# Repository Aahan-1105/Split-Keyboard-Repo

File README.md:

# Venturi - 48 Key Split Keyboard
*Code name: Model 901*

My first PCBs, first personal electronics project, and much more. This has been a lot of firsts so please excuse mistakes. Key inspiration is also mentioned below.

Steal from the best, invent the rest

## 

## Overview
The Venturi (aka model 901, venturi48) is a 48-key split, ergonomic keyboard. I can use lots of descriptors, but you can find that in the features section. 

## Contents
- All the KiCad files, including schematics and PCB
- All CAD Files including an assembly including all the components on the left side and cases for both
- ZMK firmware for Venturi
- Production files as used for production

## Images

### CAD Render

### Schematic (Left)

### PCB (Panelized)

## To-Do
- Triple-check that PCBs are good and needed components are accounted for
- PURCHASE
- Assemble and test!

## Features
- **48 Keys**  - All laptop keys within 2 layers, with additional layers for extra functionality. 
- **Wireless** - One less cable to worry about! 2x 110 maH LiPO Batteries, 2+ week battery life (estimated). Seamless multi-device operation.
- **Column Stagger** - Some mild colstag makes it more comfy to type on by better suting the different finger lengths
- **Keyboard Continuity** - Closer layout to a Macbook or general keyboard than most ergo KBs, so that you're not mad at all other keyboards while using this
- **Low Profile**  - Thinner = Better? More portable and less of an upward angle on the wrists, no need for a wrist rest 
- **Portable** - Easy on the go typing via a 3d print to easily carry it without risking damage in a backpack
- **Hot-Swappable** - Changed your mind on those clicky switches? Or maybe you're looking for a change of pace? The Venturi has you covered with hotswap switches!
- **Magsafe** - Not to wirelessly charge or to attach to the back of your phone, but for convenient tenting or to check if that coin is magnetic or not (it wasn't)

## BOM (For Hackclub Stardance Purposes)
|Purchase Status|Part                           |Qty|Price/per (CAD)|Total |Link                             |Shipping/Tax|Notes                    |
|---------------|-------------------------------|---|---------------|------|---------------------------------|------------|-------------------------|
|               |NRF52840 Dev Board             |2  |$3.95          |$7.90 |https://a.aliexpress.com/_mrUhUVZ|            |MC                       |
|               |MSK12C02 (20 pack)             |1  |$3.85          |$3.85 |https://a.aliexpress.com/_mLPJnJ1|            |Power Switch             |
|               |JST PH 2.0 Bent Plug (100 pack)|1  |$2.61          |$2.61 |https://a.aliexpress.com/_m0dvH4j|            |Battery Connector        |
|               |1N4148W Diode (100 pack)       |1  |$2.07          |$2.07 |https://a.aliexpress.com/_mNCQ5SX|            |Diodes                   |
|               |Choc Hotswap Socket (70 pack)  |1  |$10.48         |$10.48|https://a.aliexpress.com/_mq1DDpN|            |Hotswap Socket           |
|               |2.54mm socket (10 pack)        |1  |$2.64          |$2.64 |https://a.aliexpress.com/_mtOu6HZ|            |Sockets for MC           |
|               |KailH Choc Pro Red             |1  |$32.26         |$32.26|https://a.aliexpress.com/_mKtAtkx|            |Switch                   |
|               |301230 Battery JST             |2  |$5.19          |$10.38|https://a.aliexpress.com/_mt5WUH1|6.18        |Battery                  |
|               |JLCPCB PCB                     |1  |$17.73         |$17.73|                                 |12.37       |PCB (no link available)  |
|               |FNIRSI HS-02A Basic            |1  |$39.44         |$39.44|https://a.aliexpress.com/_mKQRvMj|            |Soldering Iron           |
|               |Magsafe Ring (6)               |1  |$7.51          |$7.51 |https://a.aliexpress.com/_mtm6duj|            |Magsafe Ring for Mounting|
|               |20g Lead-free solder           |1  |$5.29          |$5.29 |https://a.aliexpress.com/_mKjygpD|            |Soldering                |
|               |Flux Pen 10mL                  |1  |$4.98          |$4.98 |https://a.aliexpress.com/_mKjygpD|            |Flux for soldering       |
|               |                               |   |               |$0.00 |                                 |            |                         |
|               |                               |   |               |$0.00 |                                 |            |                         |
|               |TOTAL (CAD)                    |   |$165.69        |$0.00 |                                 |            |                         |
|               |TOTAL (USD)                    |   |$119.30        |$0.00 |                                 |            |                         |

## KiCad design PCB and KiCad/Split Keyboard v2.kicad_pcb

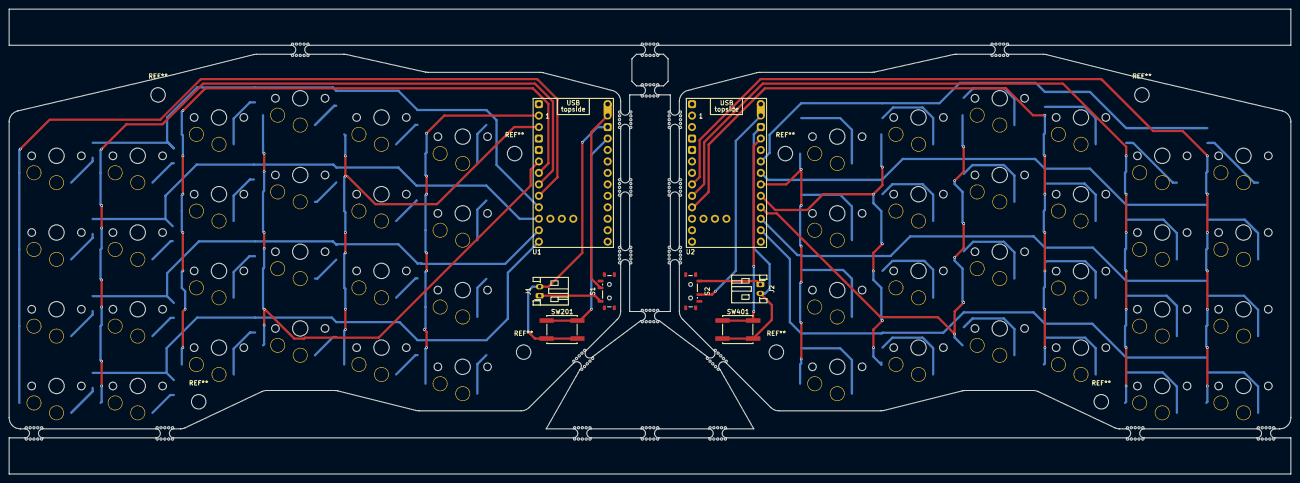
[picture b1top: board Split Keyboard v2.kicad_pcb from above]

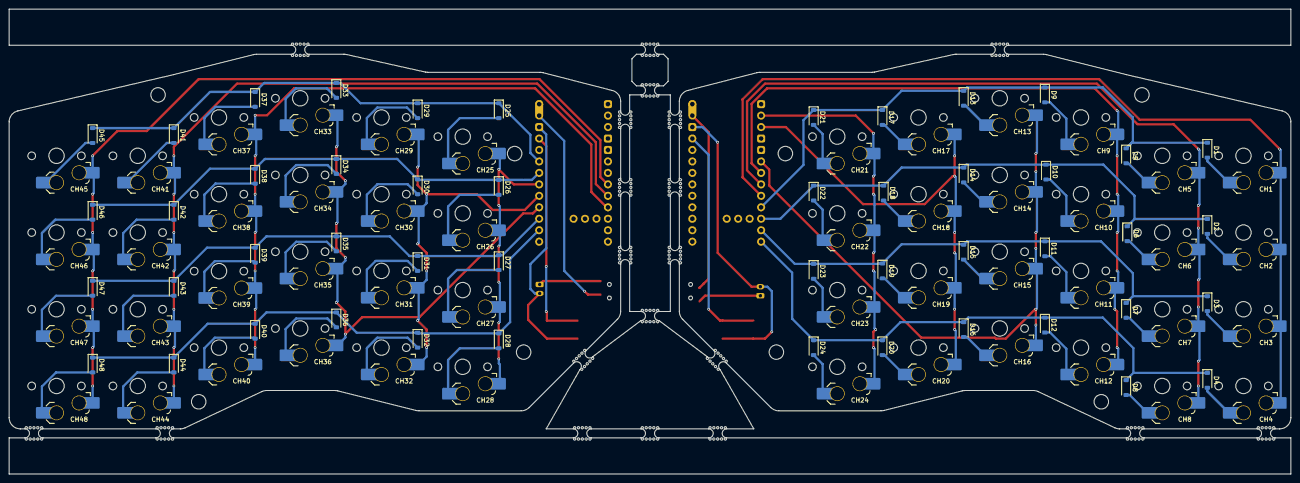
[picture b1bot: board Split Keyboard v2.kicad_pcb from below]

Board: 2 copper layers, 284.0 x 103.0 mm, 104 parts (96 on the bottom side), 76 nets.

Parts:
CH1, CH2, CH3, CH4, CH5, CH6, CH7, CH8, CH9, CH10, CH11, CH12, CH13, CH14, CH15, CH16, CH17, CH18, CH19, CH20, CH21, CH22, CH23, CH24, CH25, CH26, CH27, CH28, CH29, CH30, CH31, CH32, CH33, CH34, CH35, CH36, CH37, CH38, CH39, CH40, CH41, CH42, CH43, CH44, CH45, CH46, CH47, CH48: choc_v1_SW_HS; SW_choc_v1_HS_CPG135001S30_1u
D1, D2, D3, D4, D5, D6, D7, D8, D9, D10, D11, D12, D13, D14, D15, D16, D17, D18, D19, D20, D21, D22, D23, D24, D25, D26, D27, D28, D29, D30, D31, D32, D33, D34, D35, D36, D37, D38, D39, D40, D41, D42, D43, D44, D45, D46, D47, D48: 1N4148W; D_SOD-123
J1, J2: Conn_01x02_Socket; JST_PH_S2B-PH-K_1x02_P2.00mm_Horizontal
S1, S2: MSK12C02; SW_SPDT_Shouhan_MSK12C02
SW201, SW401: SW_SPST; SW_SPST_EVQQ2
U1, U2: nice_nano; nice_nano_AH_USBup

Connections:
/Left_Half/col1: CH21.1, CH22.1, CH23.1, CH24.1, U1.1 (P0.06)
/Left_Half/col2: CH17.1, CH18.1, CH19.1, CH20.1, U1.2 (P0.08)
/Left_Half/col3: CH13.1, CH14.1, CH15.1, CH16.1, U1.5 (P0.17)
/Left_Half/col4: CH9.1, CH10.1, CH11.1, CH12.1, U1.6 (P0.20)
/Left_Half/col5: CH5.1, CH6.1, CH7.1, CH8.1, U1.7 (P0.22)
/Left_Half/col6: CH1.1, CH2.1, CH3.1, CH4.1, U1.8 (P0.24)
/Left_Half/row1: D1.1 (K), D5.1 (K), D9.1 (K), D13.1 (K), D17.1 (K), D21.1 (K), U1.9 (P1.00)
/Left_Half/row2: D2.1 (K), D6.1 (K), D10.1 (K), D14.1 (K), D18.1 (K), D22.1 (K), U1.10 (P0.11)
/Left_Half/row3: D3.1 (K), D7.1 (K), D11.1 (K), D15.1 (K), D19.1 (K), D23.1 (K), U1.11 (P1.04-LF)
/Left_Half/row4: D4.1 (K), D8.1 (K), D12.1 (K), D16.1 (K), D20.1 (K), D24.1 (K), U1.12 (P1.06-LF)
/Right_Half/col1: CH25.1, CH26.1, CH27.1, CH28.1, U2.19 (P0.02-LF)
/Right_Half/col2: CH29.1, CH30.1, CH31.1, CH32.1, U2.20 (P1.15-LF)
/Right_Half/col3: CH33.1, CH34.1, CH35.1, CH36.1, U2.21 (P1.13-LF)
/Right_Half/col4: CH37.1, CH38.1, CH39.1, CH40.1, U2.9 (P1.00)
/Right_Half/col5: CH41.1, CH42.1, CH43.1, CH44.1, U2.8 (P0.24)
/Right_Half/col6: CH45.1, CH46.1, CH47.1, CH48.1, U2.7 (P0.22)
/Right_Half/row1: D25.1 (K), D29.1 (K), D33.1 (K), D37.1 (K), D41.1 (K), D45.1 (K), U2.17 (P0.31-LF)
/Right_Half/row2: D26.1 (K), D30.1 (K), D34.1 (K), D38.1 (K), D42.1 (K), D46.1 (K), U2.18 (P0.29-LF)
/Right_Half/row3: D27.1 (K), D31.1 (K), D35.1 (K), D39.1 (K), D43.1 (K), D47.1 (K), U2.22 (P1.11-LF)
/Right_Half/row4: D28.1 (K), D32.1 (K), D36.1 (K), D40.1 (K), D44.1 (K), D48.1 (K), U2.23 (P0.10-LF)
unnamed: CH1.2, D1.2 (A)
unnamed: CH2.2, D2.2 (A)
unnamed: CH3.2, D3.2 (A)
unnamed: CH4.2, D4.2 (A)
unnamed: CH5.2, D5.2 (A)
unnamed: CH6.2, D6.2 (A)
unnamed: CH7.2, D7.2 (A)
unnamed: CH8.2, D8.2 (A)
unnamed: CH9.2, D9.2 (A)
unnamed: CH10.2, D10.2 (A)
unnamed: CH11.2, D11.2 (A)
unnamed: CH12.2, D12.2 (A)
unnamed: CH13.2, D13.2 (A)
unnamed: CH14.2, D14.2 (A)
unnamed: CH15.2, D15.2 (A)
unnamed: CH16.2, D16.2 (A)
unnamed: CH17.2, D17.2 (A)
unnamed: CH18.2, D18.2 (A)
unnamed: CH19.2, D19.2 (A)
unnamed: CH20.2, D20.2 (A)
unnamed: CH21.2, D21.2 (A)
unnamed: CH22.2, D22.2 (A)
unnamed: CH23.2, D23.2 (A)
unnamed: CH24.2, D24.2 (A)
unnamed: CH25.2, D25.2 (A)
unnamed: CH26.2, D26.2 (A)
unnamed: CH27.2, D27.2 (A)
unnamed: CH28.2, D28.2 (A)
unnamed: CH29.2, D29.2 (A)
unnamed: CH30.2, D30.2 (A)
unnamed: CH31.2, D31.2 (A)
unnamed: CH32.2, D32.2 (A)
unnamed: CH33.2, D33.2 (A)
unnamed: CH34.2, D34.2 (A)
unnamed: CH35.2, D35.2 (A)
unnamed: CH36.2, D36.2 (A)
unnamed: CH37.2, D37.2 (A)
unnamed: CH38.2, D38.2 (A)
unnamed: CH39.2, D39.2 (A)
unnamed: CH40.2, D40.2 (A)
unnamed: CH41.2, D41.2 (A)
unnamed: CH42.2, D42.2 (A)
unnamed: CH43.2, D43.2 (A)
unnamed: CH44.2, D44.2 (A)
unnamed: CH45.2, D45.2 (A)
unnamed: CH46.2, D46.2 (A)
unnamed: CH47.2, D47.2 (A)
unnamed: CH48.2, D48.2 (A)
unnamed: J1.1, S1.1
unnamed: J1.2, SW201.2 (B), U1.14 (GND)
unnamed: J2.1, S2.1
unnamed: J2.2, SW401.2 (B), U2.14 (GND)
unnamed: S1.2, U1.13 (BAT+)
unnamed: S2.2, U2.13 (BAT+)
unnamed: SW201.1 (A), U1.15 (RST)
unnamed: SW401.1 (A), U2.15 (RST)
